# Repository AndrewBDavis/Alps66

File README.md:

ALPS 66% keyboard PCB
=====================
The primary goal of this project was to design a PCB and plate which fits in KBD66 and FC660m cases and supports FC660m, FC660c and 66% AEK style layouts.
The pcb schematic is modified from Hasu's Alps64.

Shown in FC660M case with prototype 1.2mm FR4 Plate in FC660C Layout

Supported Layouts
---------------
No ISO Enter (Especially ISO AEK)

Rev1 boards only:
	To utilize split backspace or 3rd key to the right of spacebar, you will need to solder bridge SJ1.
	To utilize the LED indicator, you will need to solder bridge SJ2 and modify files. 

Bottom row:
	1.5__1.0___1.5___6.5___1.5___1.5___1__1__1		(AEK with and 1u option key)

	1.5__1.25__1.5___6.25__1.5___1.5___1__1__1		(AEK Standard with 6.25 spacebar)

	1.5__1.25__1.5___5__1.5___1.25___1.5___1__1__1		(AEK Standard with 5 spacebar)
	
	1.25__1.25__1.25__6__1.25__1.25__1.25__1__1__1		(FC660c bottom row)
	
	1.25__1.0___1.25__6.25__1.25__1.25__1.25__1__1__1	(FC660m bottom row)

Caps lock:  
	0.75u  (Non Stepped)  
	0.25u  (Alps Dell/SGI Stepped)  
	0.125u (Cherry Stepped)  

Where key unit for rows: Esc[0u], 1[1u]...

Supported Cases
-------------
KBDFans KBD66 (confirmed)  
Leopold FC660m (confirmed)  
KBDFans KBD661 (unconfirmed)  

BOM for Alps66 keyboard                                                  
------------------
| REF:  | VALUE:     | FOOTPRINT:           | COMPONENT            |
|------ | ---------- | -------------------- | -------------------- |  
| C1    | 4.7u       | C_0805               |                      |
| C2    | 1u         | C_0805               |                      |     
| C3    | 22p        | C_0805               |                      |
| C4    | 22p        | C_0805               |                      |
| C5    | 0.1u       | C_0805               |                      |
| C6    | 0.1u       | C_0805               |                      |
| J1    | USB_mini_B | USB_miniB_hirose_5S8 | UX60SC-MB-5S8 Hirose |
| R1    | 22         | R_0805               |                      |
| R2    | 22         | R_0805               |                      |
| R3    | 10K        | R_0805               |                      |
| R4    | 1K         | R_0805               |                      |
| R5    | 10K        | R_0805               |                      |
| SW100 | SW_PUSH    | SW_SPST_B3U-1000P-B  | B3U-1000P-B          |
| U1    | ATMEGA32U2 | QFP32                | ATMega32u2-AU        | 
| X1    | CRYSTAL    | FA-238               | 16MHz, 12PF          |
| D(67) | DIODE      | SOD-123 or Axial     | 1N4148               |
| LED1  | LED        | LED_D3.0mm           | 3mm Round Top LED    |

Revisions
-------------
V1.0: 	Initial Release  
V2.0: 	The switch holes are reduced from 2.05mm, no longer supporting 8134-HC-12P2 / 8134-HC-12P3 holtite sockets.  
&emsp;&emsp;&nbsp;&nbsp;Crystal Load Capacitance changed from 10pF to 12pF  
&emsp;&emsp;&nbsp;&nbsp;Changed C1 package size from 1206 to 0805  
&emsp;&emsp;&nbsp;&nbsp;Changed footprint library from Hasu's keyboard_parts to personal "Keyboard_Footprints" library  
&emsp;&emsp;&nbsp;&nbsp;Change ground plane configuration  
&emsp;&emsp;&nbsp;&nbsp;Moved diode D15 to allow added mounting location between K15 and K16  
&emsp;&emsp;&nbsp;&nbsp;Removed wider 6u stabilizer footprint spacing, narrower footprint is supported by SP and GMK  
&emsp;&emsp;&nbsp;&nbsp;Changed SMD led to standard through hole, adding provistions for SKCL in-switch LED on Esc key  
&emsp;&emsp;&nbsp;&nbsp;Changed matrix and removed solder jumpers  
&emsp;&emsp;&nbsp;&nbsp;Added Support for 1.5,1.25,1.5,5,1.5,1.25,1.5,1,1,1 bottom row

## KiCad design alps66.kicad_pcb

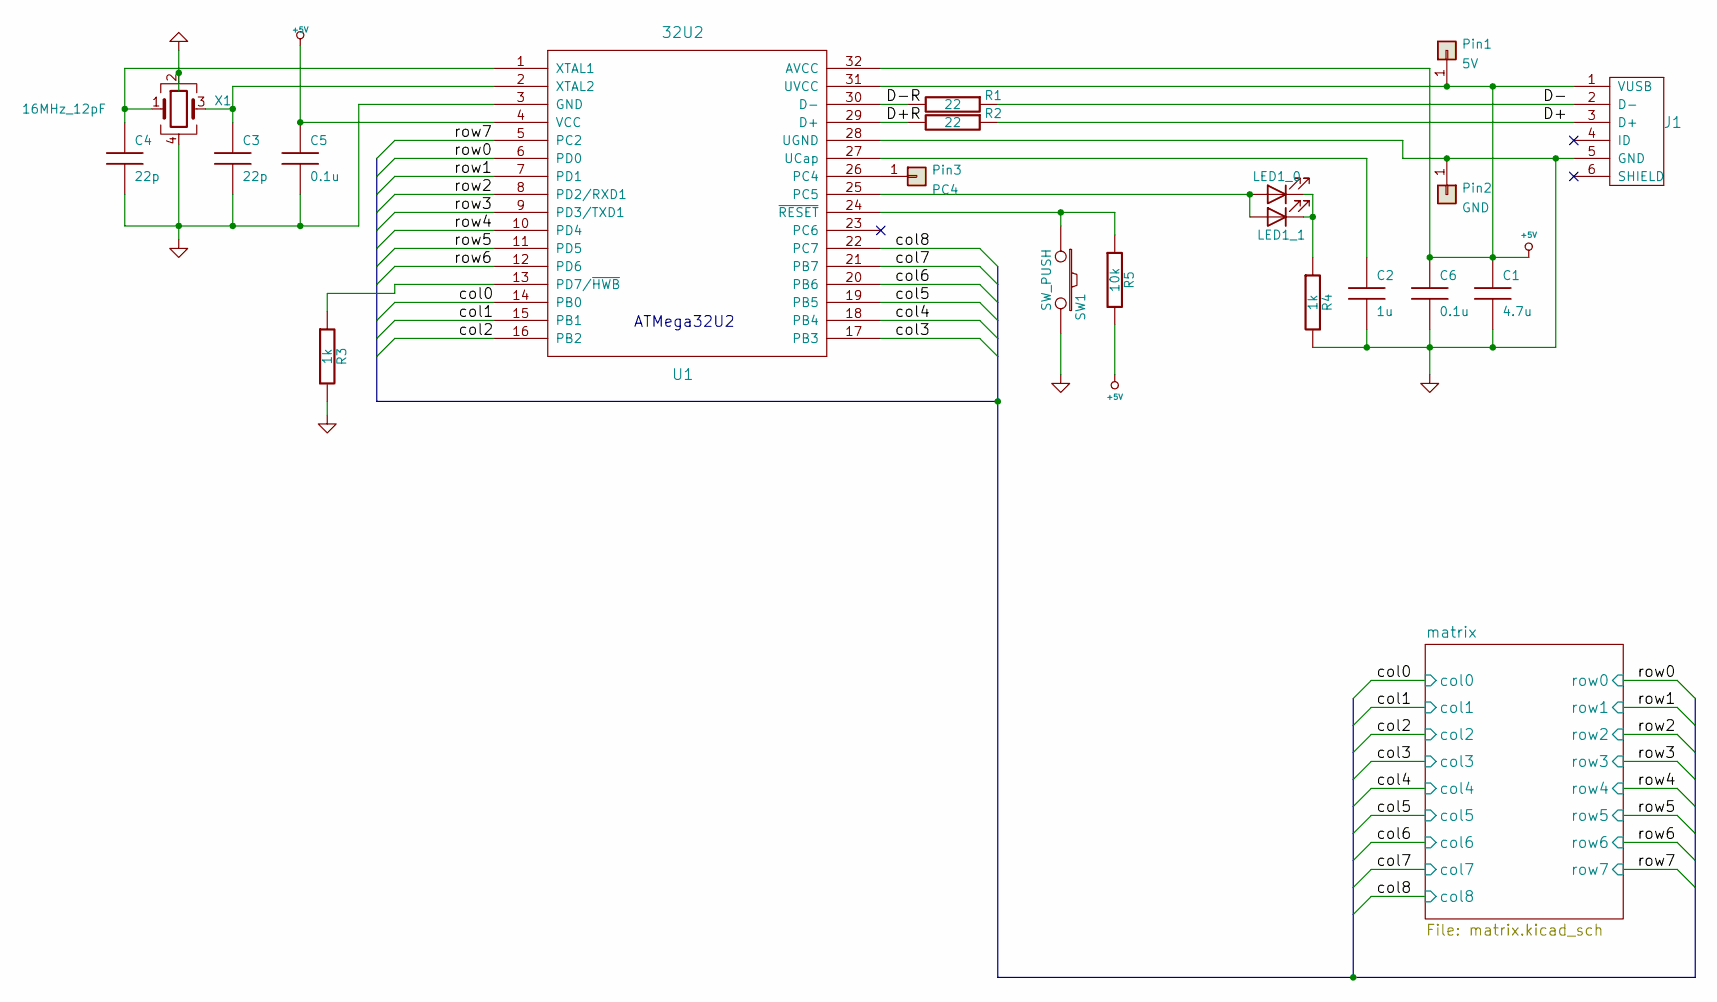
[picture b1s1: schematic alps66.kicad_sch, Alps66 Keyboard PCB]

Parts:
C1: 4.7u; C_0805_2012Metric
C2: 1u; C_0805_2012Metric
C3, C4: 22p; C_0805_2012Metric
C5, C6: 0.1u; C_0805_2012Metric
J1: USB_mini_micro_B; USB_miniB_hirose_5S8
LED1_0: 3mm; LED_D3.0mm
LED1_1: 5mm_Rectangular; LED_Rectangular_W5.0mm_H2.0mm
Pin1: 5V; Pin
Pin2: GND; Pin
Pin3: PC4; Pin
R1, R2: 22; R_0805_2012Metric
R3, R4: 1k; R_0805_2012Metric
R5: 10k; R_0805_2012Metric
SW1: SW_PUSH; SW_SPST_B3U-1000P-B
U1: 32U2; LQFP-32_7x7mm_P0.8mm
X1: 16MHz_12pF; Crystal_SMD_SeikoEpson_FA238-4Pin_3.2x2.5mm

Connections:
+5V: C1.1, C5.1, C6.1, J1.1 (VUSB), Pin1.1, R5.2, U1.4 (VCC), U1.31 (UVCC), U1.32 (AVCC)
/D+: J1.3 (D+), R2.1
/D+R: R2.2, U1.29 (D+)
/D-: J1.2 (D-), R1.1
/D-R: R1.2, U1.30 (D-)
/col0: U1.14 (PB0); also elsewhere on the board
/col1: U1.15 (PB1); also elsewhere on the board
/col2: U1.16 (PB2); also elsewhere on the board
/col3: U1.17 (PB3); also elsewhere on the board
/col4: U1.18 (PB4); also elsewhere on the board
/col5: U1.19 (PB5); also elsewhere on the board
/col6: U1.20 (PB6); also elsewhere on the board
/col7: U1.21 (PB7); also elsewhere on the board
/col8: U1.22 (PC7); also elsewhere on the board
/row0: U1.6 (PD0); also elsewhere on the board
/row1: U1.7 (PD1); also elsewhere on the board
/row2: U1.8 (PD2/RXD1); also elsewhere on the board
/row3: U1.9 (PD3/TXD1); also elsewhere on the board
/row4: U1.10 (PD4); also elsewhere on the board
/row5: U1.11 (PD5); also elsewhere on the board
/row6: U1.12 (PD6); also elsewhere on the board
/row7: U1.5 (PC2); also elsewhere on the board
GND: C1.2, C2.2, C3.2, C4.2, C5.2, C6.2, J1.5 (GND), Pin2.1, R3.2, R4.2, SW1.2, U1.3 (GND), U1.28 (UGND), X1.2, X1.4
unnamed: C2.1, U1.27 (UCap)
unnamed: C3.1, U1.2 (XTAL2), X1.3
unnamed: C4.1, U1.1 (XTAL1), X1.1
unnamed: LED1_0.1 (K), LED1_1.1 (K), R4.1
unnamed: LED1_0.2 (A), LED1_1.2 (A), U1.25 (PC5)
unnamed: Pin3.1, U1.26 (PC4)
unnamed: R3.1, U1.13 (PD7/~HWB)
unnamed: R5.1, SW1.1, U1.24 (~RESET)

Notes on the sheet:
ATMega32U2

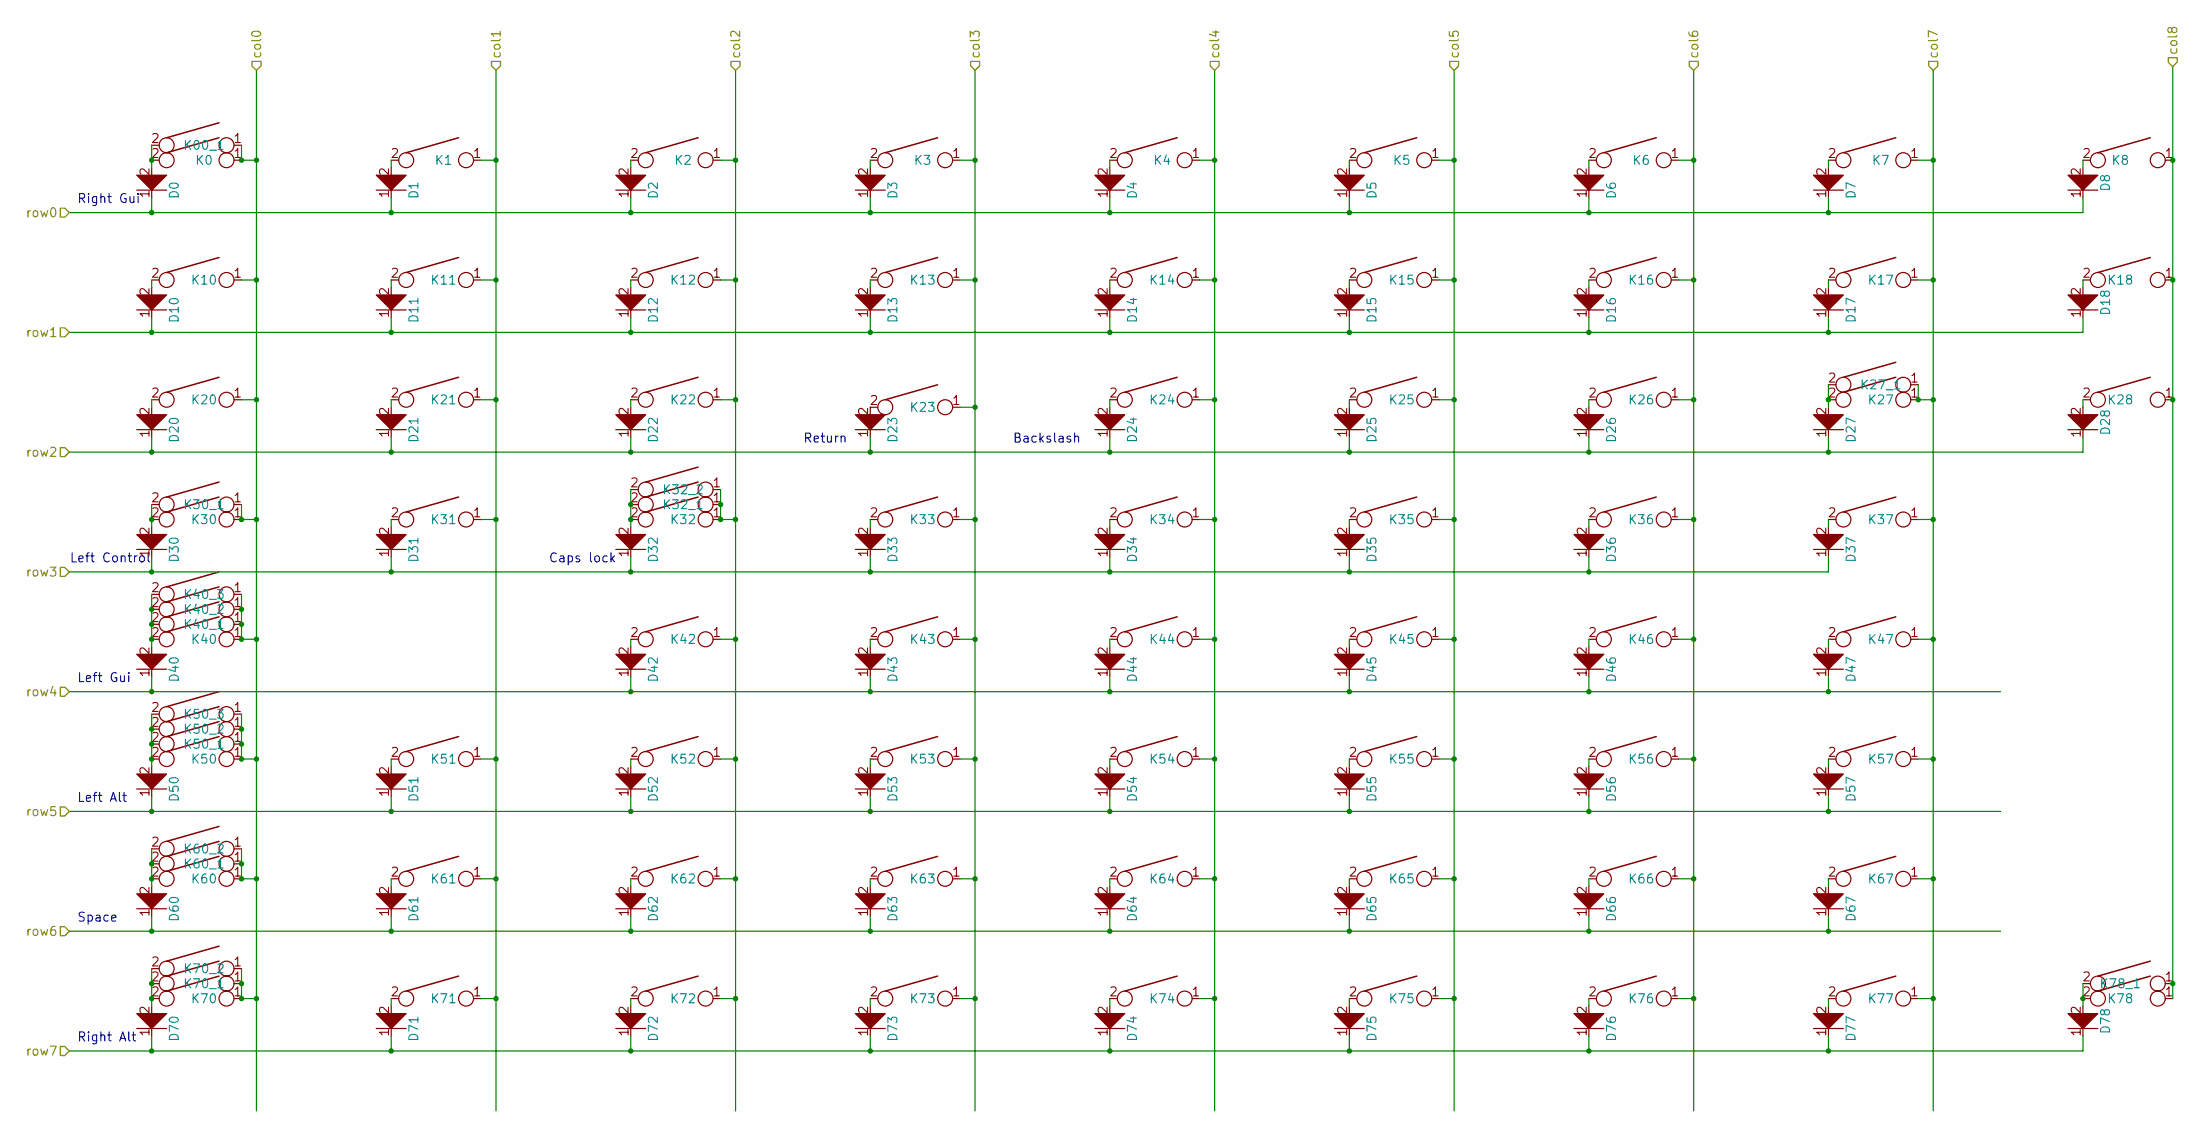
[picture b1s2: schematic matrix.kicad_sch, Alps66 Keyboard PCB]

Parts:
D0, D1, D2, D3, D4, D5, D6, D7, D8, D10, D11, D12, D13, D14, D15, D16, D17, D18, D20, D21, D22, D23, D24, D25, D26, D27, D28, D30, D31, D32, D33, D34, D35, D36, D37, D40, D42, D43, D44, D45, D46, D47, D50, D51, D52, D53, D54, D55, D56, D57, D60, D61, D62, D63, D64, D65, D66, D67, D70, D71, D72, D73, D74, D75, D76, D77, D78: D; Diode_123_Axial
K0, K1, K2, K3, K4, K5, K6, K7, K8, K10, K11, K12, K13, K14, K15, K16, K17, K18, K20, K21, K22, K23, K24, K25, K26, K27, K28, K30, K31, K32, K33, K34, K35, K36, K37, K40, K42, K43, K44, K45, K46, K47, K50, K51, K52, K53, K54, K55, K56, K57, K60, K61, K62, K63, K64, K65, K66, K67, K70, K71, K72, K73, K74, K75, K76, K77, K78: KEYSW; Alps
K00_1, K27_1, K30_1, K32_1, K32_2, K40_1, K40_2, K40_3, K50_3, K70_1: KEYSW; Alps_Secondary
K50_1, K50_2, K60_1, K60_2, K70_2, K78_1: KEYSW; Alps_Secondary_Reversed

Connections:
/col0: K0.1, K00_1.1, K10.1, K20.1, K30.1, K30_1.1, K40.1, K40_1.1, K40_2.1, K40_3.1, K50.1, K50_1.1, K50_2.1, K50_3.1, K60.1, K60_1.1, K60_2.1, K70.1, K70_1.1, K70_2.1; also elsewhere on the board
/col1: K1.1, K11.1, K21.1, K31.1, K51.1, K61.1, K71.1; also elsewhere on the board
/col2: K2.1, K12.1, K22.1, K32.1, K32_1.1, K32_2.1, K42.1, K52.1, K62.1, K72.1; also elsewhere on the board
/col3: K3.1, K13.1, K23.1, K33.1, K43.1, K53.1, K63.1, K73.1; also elsewhere on the board
/col4: K4.1, K14.1, K24.1, K34.1, K44.1, K54.1, K64.1, K74.1; also elsewhere on the board
/col5: K5.1, K15.1, K25.1, K35.1, K45.1, K55.1, K65.1, K75.1; also elsewhere on the board
/col6: K6.1, K16.1, K26.1, K36.1, K46.1, K56.1, K66.1, K76.1; also elsewhere on the board
/col7: K7.1, K17.1, K27.1, K27_1.1, K37.1, K47.1, K57.1, K67.1, K77.1; also elsewhere on the board
/col8: K8.1, K18.1, K28.1, K78.1, K78_1.1; also elsewhere on the board
/row0: D0.1, D1.1, D2.1, D3.1, D4.1, D5.1, D6.1, D7.1, D8.1; also elsewhere on the board
/row1: D10.1, D11.1, D12.1, D13.1, D14.1, D15.1, D16.1, D17.1, D18.1; also elsewhere on the board
/row2: D20.1, D21.1, D22.1, D23.1, D24.1, D25.1, D26.1, D27.1, D28.1; also elsewhere on the board
/row3: D30.1, D31.1, D32.1, D33.1, D34.1, D35.1, D36.1, D37.1; also elsewhere on the board
/row4: D40.1, D42.1, D43.1, D44.1, D45.1, D46.1, D47.1; also elsewhere on the board
/row5: D50.1, D51.1, D52.1, D53.1, D54.1, D55.1, D56.1, D57.1; also elsewhere on the board
/row6: D60.1, D61.1, D62.1, D63.1, D64.1, D65.1, D66.1, D67.1; also elsewhere on the board
/row7: D70.1, D71.1, D72.1, D73.1, D74.1, D75.1, D76.1, D77.1, D78.1; also elsewhere on the board
unnamed: D0.2, K0.2, K00_1.2
unnamed: D1.2, K1.2
unnamed: D2.2, K2.2
unnamed: D3.2, K3.2
unnamed: D4.2, K4.2
unnamed: D5.2, K5.2
unnamed: D6.2, K6.2
unnamed: D7.2, K7.2
unnamed: D8.2, K8.2
unnamed: D10.2, K10.2
unnamed: D11.2, K11.2
unnamed: D12.2, K12.2
unnamed: D13.2, K13.2
unnamed: D14.2, K14.2
unnamed: D15.2, K15.2
unnamed: D16.2, K16.2
unnamed: D17.2, K17.2
unnamed: D18.2, K18.2
unnamed: D20.2, K20.2
unnamed: D21.2, K21.2
unnamed: D22.2, K22.2
unnamed: D23.2, K23.2
unnamed: D24.2, K24.2
unnamed: D25.2, K25.2
unnamed: D26.2, K26.2
unnamed: D27.2, K27.2, K27_1.2
unnamed: D28.2, K28.2
unnamed: D30.2, K30.2, K30_1.2
unnamed: D31.2, K31.2
unnamed: D32.2, K32.2, K32_1.2, K32_2.2
unnamed: D33.2, K33.2
unnamed: D34.2, K34.2
unnamed: D35.2, K35.2
unnamed: D36.2, K36.2
unnamed: D37.2, K37.2
unnamed: D40.2, K40.2, K40_1.2, K40_2.2, K40_3.2
unnamed: D42.2, K42.2
unnamed: D43.2, K43.2
unnamed: D44.2, K44.2
unnamed: D45.2, K45.2
unnamed: D46.2, K46.2
unnamed: D47.2, K47.2
unnamed: D50.2, K50.2, K50_1.2, K50_2.2, K50_3.2
unnamed: D51.2, K51.2
unnamed: D52.2, K52.2
unnamed: D53.2, K53.2
unnamed: D54.2, K54.2
unnamed: D55.2, K55.2
unnamed: D56.2, K56.2
unnamed: D57.2, K57.2
unnamed: D60.2, K60.2, K60_1.2, K60_2.2
unnamed: D61.2, K61.2
unnamed: D62.2, K62.2
unnamed: D63.2, K63.2
unnamed: D64.2, K64.2
unnamed: D65.2, K65.2
unnamed: D66.2, K66.2
unnamed: D67.2, K67.2
unnamed: D70.2, K70.2, K70_1.2, K70_2.2
unnamed: D71.2, K71.2
unnamed: D72.2, K72.2
unnamed: D73.2, K73.2
unnamed: D74.2, K74.2
unnamed: D75.2, K75.2
unnamed: D76.2, K76.2
unnamed: D77.2, K77.2
unnamed: D78.2, K78.2, K78_1.2

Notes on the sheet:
Backslash
Left Gui
Right Gui
Caps lock
Left Control
Space
Return
Left Alt
Right Alt

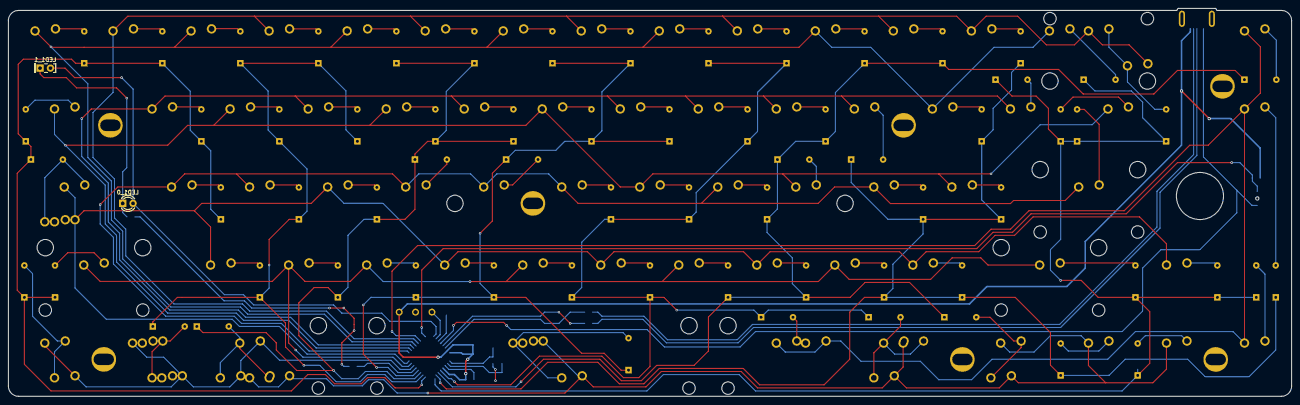
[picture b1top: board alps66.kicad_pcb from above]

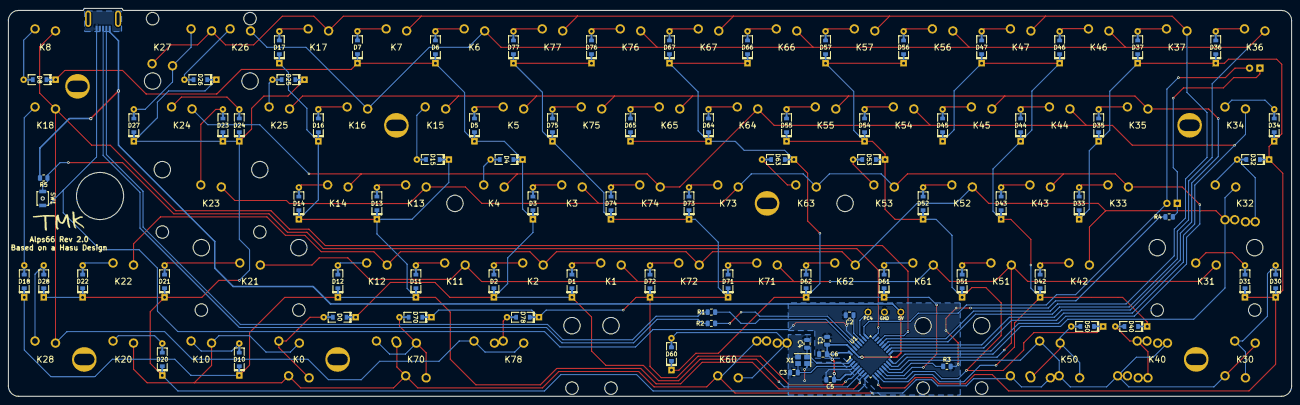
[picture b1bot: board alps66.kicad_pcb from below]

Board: 2 copper layers, 313.3 x 94.7 mm, 183 parts (82 on the bottom side), 98 nets.

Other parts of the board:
2u, 2u#2, 2u#3, 2u#4: 2u_stab
6.25u_stab: 6.25u_stab
6u_stab: 6u_stab_SP
Oval_Mounting_Hole: Oval_Mounting_Hole
Oval_Mounting_Hole#2, Oval_Mounting_Hole#3, Oval_Mounting_Hole#4, Oval_Mounting_Hole#5, Oval_Mounting_Hole#6, Oval_Mounting_Hole#7: Oval_Mounting_Hole

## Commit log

2019-09-24 Rename READ.me to README.me
2019-09-24 Rename README.me to README.md
2022-03-14 3/14/21
2022-03-14 Initial Release
2022-03-14 directory changes
2022-03-18 Update Axial_Diode Footprint
